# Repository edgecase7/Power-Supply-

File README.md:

This is a power supply made by our team of 3 people ( Me, Lord Piyush , and Vipul Don)

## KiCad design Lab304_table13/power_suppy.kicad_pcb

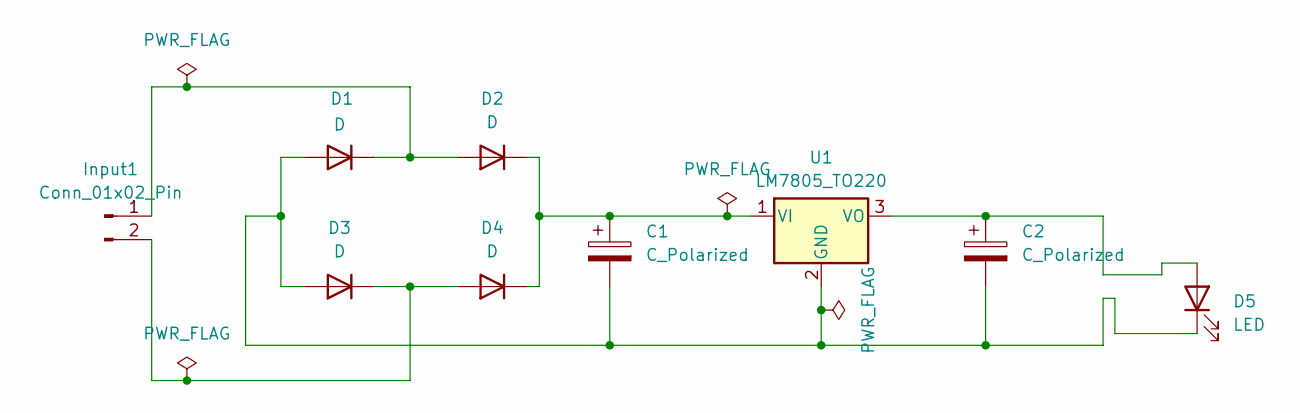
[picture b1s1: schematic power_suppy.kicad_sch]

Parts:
C1, C2: C_Polarized; CP_Radial_D4.0mm_P1.50mm
D1, D2, D3, D4: D; D_DO-41_SOD81_P7.62mm_Horizontal
D5: LED; LED_D5.0mm
Input1: Conn_01x02_Pin; JST_EH_B2B-EH-A_1x02_P2.50mm_Vertical
U1: LM7805_TO220; TO-220-3_Vertical

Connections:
unnamed: C1.2, C2.2, D1.2 (A), D3.2 (A), D5.1 (K), U1.2 (GND)
unnamed: D1.1 (K), D2.2 (A), Input1.1
unnamed: C1.1, D2.1 (K), D4.1 (K), U1.1 (VI)
unnamed: D3.1 (K), D4.2 (A), Input1.2
unnamed: C2.1, D5.2 (A), U1.3 (VO)

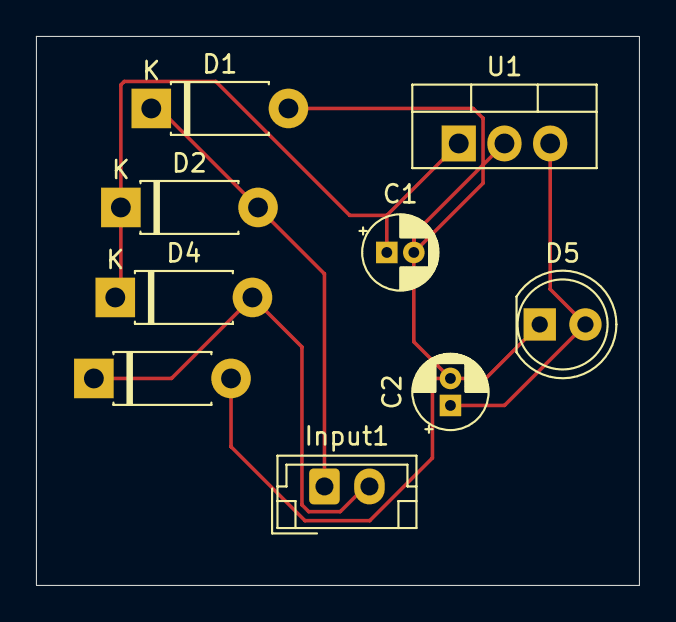
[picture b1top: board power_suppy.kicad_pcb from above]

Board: 2 copper layers, 33.5 x 30.5 mm, 9 parts (0 on the bottom side), 5 nets.
